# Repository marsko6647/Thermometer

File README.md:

Bygger en termometer för att mäta inomhus- och utomhustemperatur egentligen bara i syfte att lära mig KiCad.

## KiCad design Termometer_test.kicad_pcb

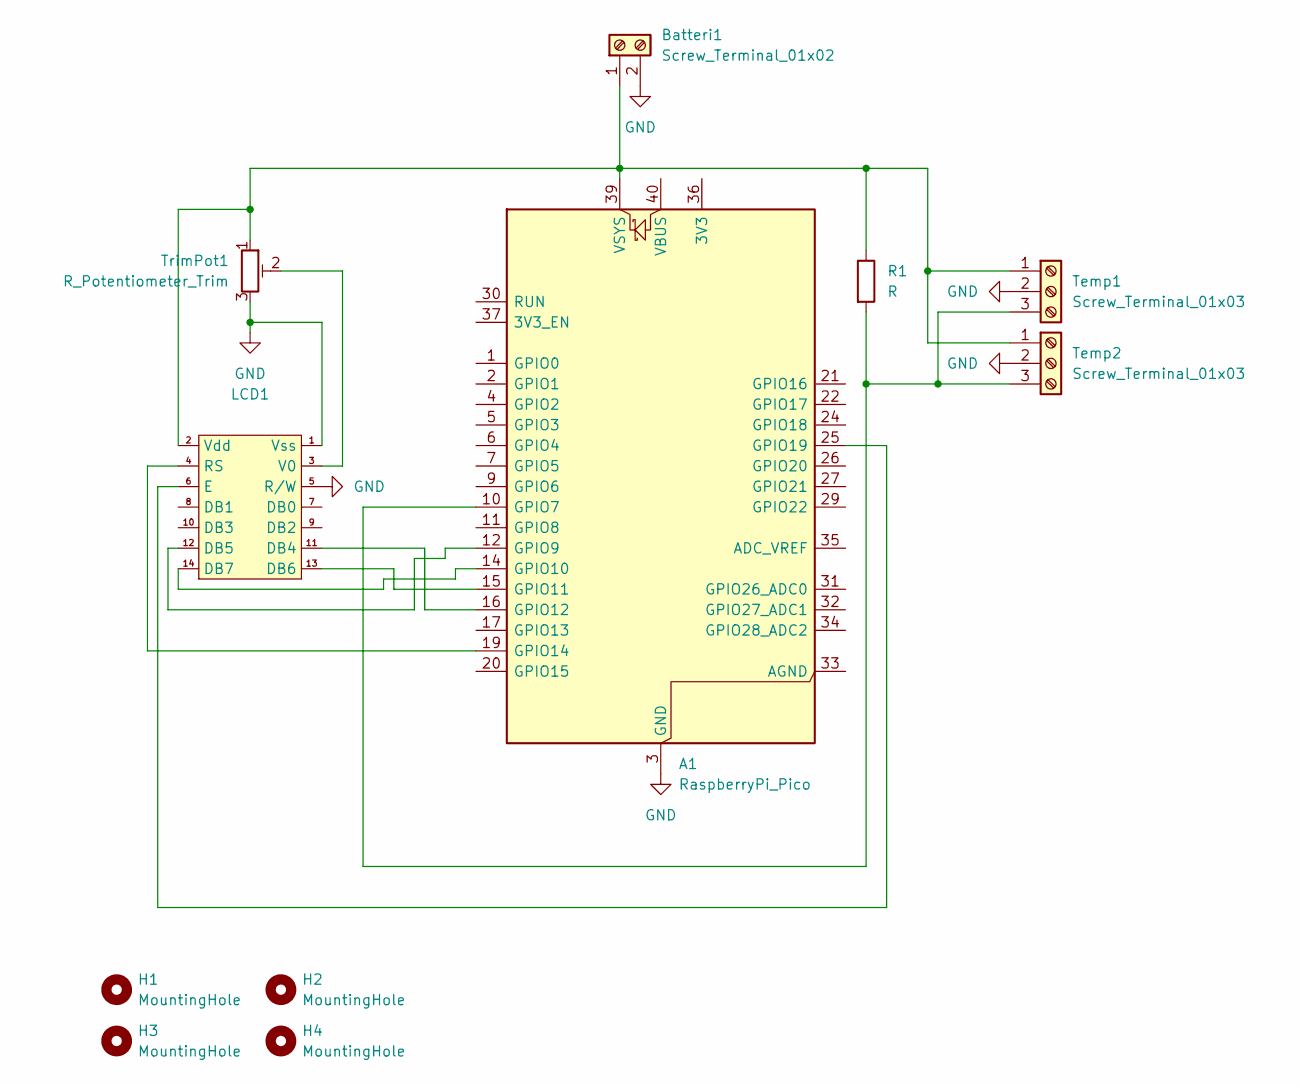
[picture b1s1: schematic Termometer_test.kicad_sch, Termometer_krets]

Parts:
A1: RaspberryPi_Pico; RaspberryPi_Pico_Common_Unspecified
Batteri1: Screw_Terminal_01x02; TerminalBlock_MaiXu_MX126-5.0-02P_1x02_P5.00mm
H1, H2, H3, H4: MountingHole; MountingHole_3.2mm_M3_DIN965_Pad
LCD1: LCD
R1: R; R_Axial_DIN0204_L3.6mm_D1.6mm_P7.62mm_Horizontal
Temp1, Temp2: Screw_Terminal_01x03; TerminalBlock_MaiXu_MX126-5.0-03P_1x03_P5.00mm
TrimPot1: R_Potentiometer_Trim; Potentiometer_Runtron_RM-065_Vertical

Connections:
GND: A1.3 (GND), A1.8 (GND), A1.13 (GND), A1.18 (GND), A1.23 (GND), A1.28 (GND), A1.38 (GND), Batteri1.2, LCD1.1 (Vss), LCD1.5 (R/W), Temp1.2, Temp2.2, TrimPot1.3
unnamed: A1.10 (GPIO7), R1.2, Temp1.3, Temp2.3
unnamed: A1.12 (GPIO9), LCD1.12 (DB5)
unnamed: A1.14 (GPIO10), LCD1.14 (DB7)
unnamed: A1.15 (GPIO11), LCD1.13 (DB6)
unnamed: A1.16 (GPIO12), LCD1.11 (DB4)
unnamed: A1.19 (GPIO14), LCD1.4 (RS)
unnamed: A1.25 (GPIO19), LCD1.6 (E)
unnamed: A1.39 (VSYS), Batteri1.1, LCD1.2 (Vdd), R1.1, Temp1.1, Temp2.1, TrimPot1.1
unnamed: LCD1.3 (V0), TrimPot1.2

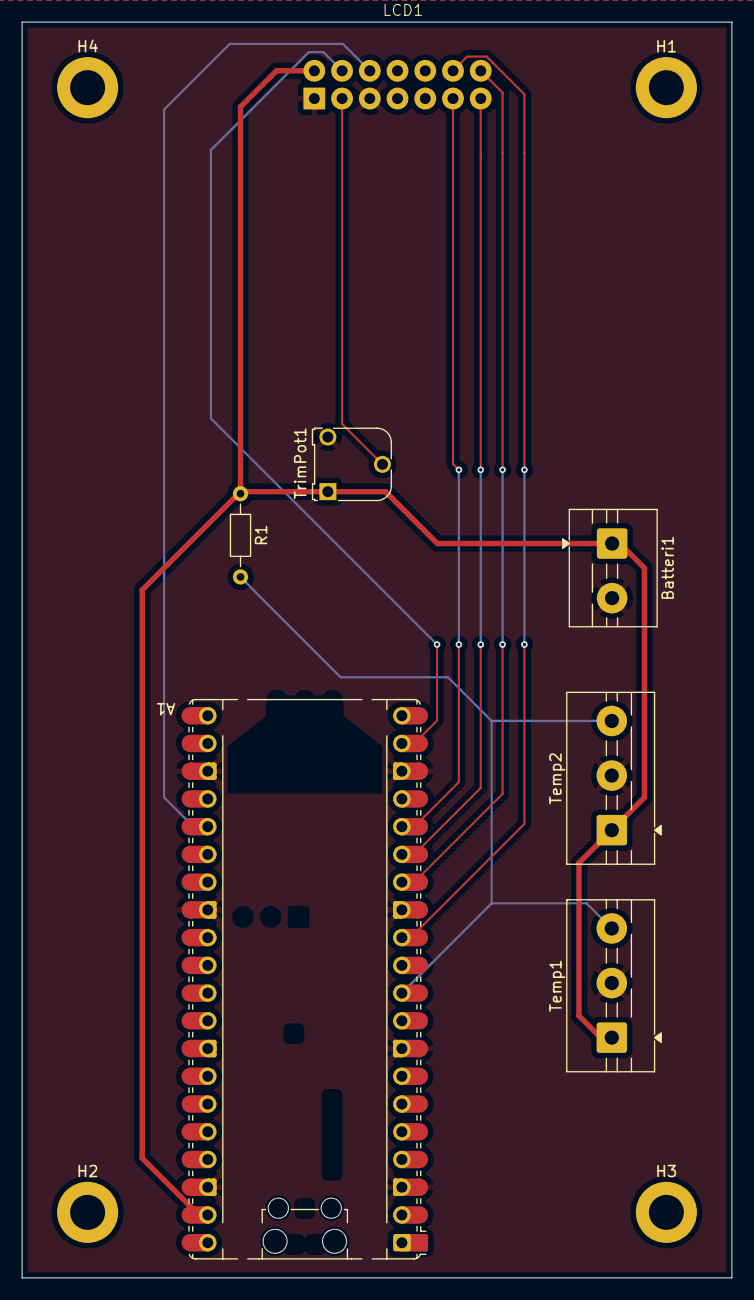
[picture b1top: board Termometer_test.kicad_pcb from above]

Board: 2 copper layers, 65.0 x 115.0 mm, 11 parts (0 on the bottom side), 10 nets.

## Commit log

2026-02-05 Add project description for thermometer build
